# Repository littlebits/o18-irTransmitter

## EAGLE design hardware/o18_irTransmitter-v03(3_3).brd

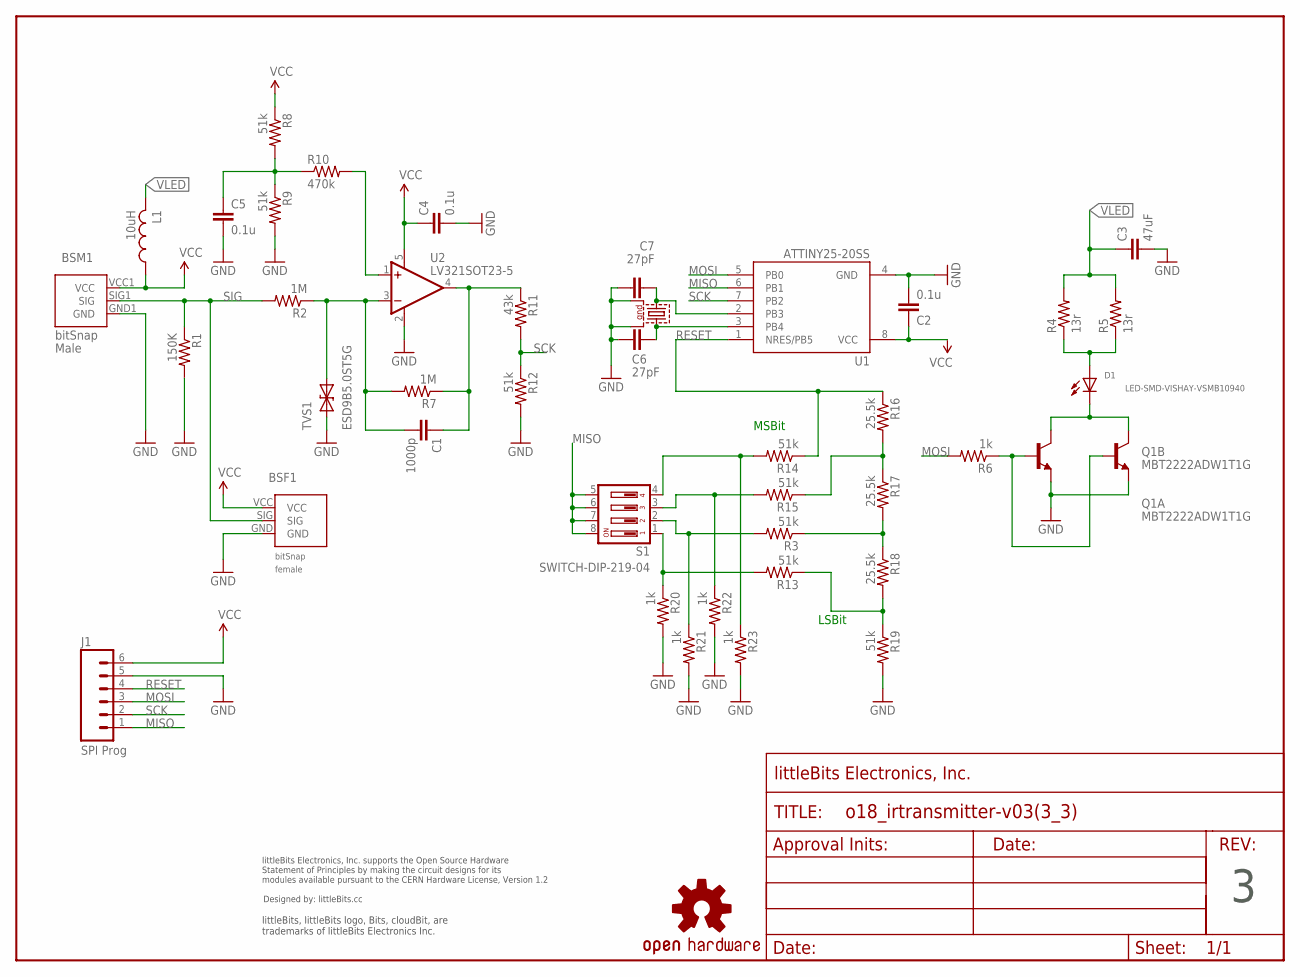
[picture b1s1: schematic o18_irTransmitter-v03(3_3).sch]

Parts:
BSF1: BITSNAP_V03_FEMALE
BSM1: BITSNAP_V03_MALE
C1: 1000p; CAP-0402
C2, C4, C5: 0.1u; CAP-0402
C3: 47uF; CAP-1206
C6, C7: 27pF; CAP-0402
D1: LED-SMD-VISHAY-VSMB10940
J1: SPI Prog; SIP6-SM-0.1IN-NOS.S-MIN
L1: 10uH; IND-0805
Q1: MBT2222ADW1T1G; SOT-363_ONSEMI
R1: 150K; RES-0402
R2, R7: 1M; RES-0402
R3, R8, R9, R12, R13, R14, R15, R19: 51k; RES-0402
R4, R5: 13r; RES-0603
R6, R20, R21, R22, R23: 1k; RES-0402
R10: 470k; RES-0402
R11: 43k; RES-0402
R16, R17, R18: 25.5k; RES-0402
S1: SWITCH-DIP-219-04; CTS-219-04
TVS1: ESD9B5.0ST5G; SOD-923
U1: ATTINY25-20SS; SOIC08_JEDEC_150MIL
U2: LV321SOT23-5; SOT23-5
U$16: OSHWCREDIT
U$26: FRAME-LETTER-OHWOHW; FABDWG01-OHW
U$27: OSHW-LOGOL; OSHW-LOGO-L
X1: 7B-8.000MAAJ-T; CRYSTAL-SMD-7B-SERIES-5X3.2MM

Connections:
GND: BSF1.GND, BSM1.GND1 (GND), C2.2, C3.2, C4.2, C5.2, C6.2, C7.1, J1.5, Q1.1 (E), Q1.4 (E), R1.2, R9.2, R12.2, R19.2, R20.2, R21.2, R22.2, R23.2, TVS1.1 (A), U1.4 (GND), U2.2 (V-), X1.P$2 (2), X1.P$4 (4)
MISO: J1.1, S1.5, S1.6, S1.7, S1.8, U1.6 (PB1)
MOSI: J1.3, R6.2, U1.5 (PB0)
unnamed: D1.C, Q1.3 (C), Q1.6 (C)
unnamed: Q1.2 (B), Q1.5 (B), R6.1
unnamed: D1.A, R4.1, R5.1
unnamed: C1.2, R2.1, R7.2, TVS1.2 (C), U2.3 (-IN)
unnamed: R10.2, U2.1 (+IN)
unnamed: C5.1, R8.2, R9.1, R10.1
unnamed: C1.1, R7.1, R11.1, U2.4 (OUT)
unnamed: C7.2, U1.2 (PB3), X1.P$1 (1)
unnamed: C6.1, U1.3 (PB4), X1.P$3 (3)
unnamed: R3.2, R21.1, S1.2
unnamed: R14.2, R23.1, S1.4
unnamed: R15.2, R22.1, S1.3
unnamed: R13.2, R20.1, S1.1
unnamed: R3.1, R17.2, R18.1
unnamed: R13.1, R18.2, R19.1
unnamed: R15.1, R16.2, R17.1
RESET: J1.4, R14.1, R16.1, U1.1 (NRES/PB5)
SCK: J1.2, R11.2, R12.1, U1.7 (PB2)
SIG: BSF1.SIG, BSM1.SIG1 (SIG), R1.1, R2.2
VCC: BSF1.VCC, BSM1.VCC1 (VCC), C2.1, C4.1, J1.6, L1.1, R8.1, U1.8 (VCC), U2.5 (V+)
VLED: C3.1, L1.2, R4.2, R5.2

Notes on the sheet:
MSBit
LSBit

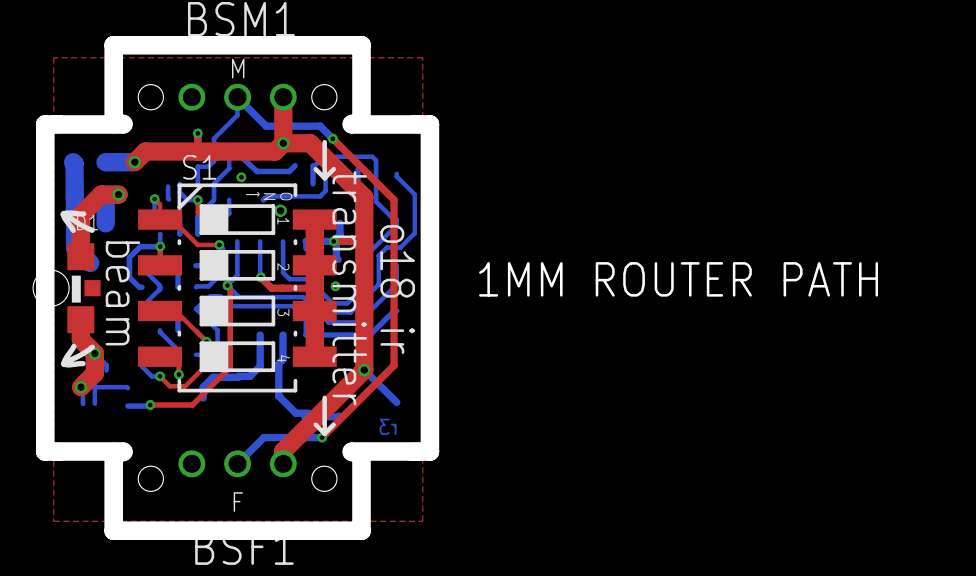
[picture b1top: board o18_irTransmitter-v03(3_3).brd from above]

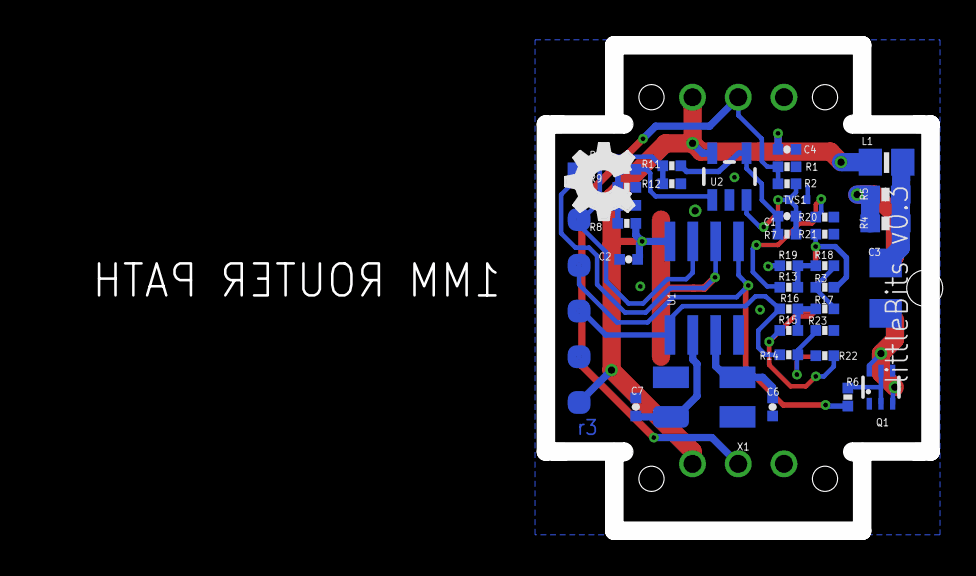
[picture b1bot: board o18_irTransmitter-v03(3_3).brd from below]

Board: 2 copper layers, 49.2 x 27.0 mm, 50 parts (38 on the bottom side), 24 nets.

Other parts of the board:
DRILEGEND: DRILEGEND
U$4, U$21: <
U$5, U$22: L
U$20: OSHW_FILLX150_NOTEXT

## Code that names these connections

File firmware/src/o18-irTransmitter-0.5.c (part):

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	CLKPR = 0x80;		// This two byte combination undoes the CLKDIV setting and sets the clock prescaler to 1,
	CLKPR = 0x00;		// giving us a clock frequency of 8Mhz

	DDRB = ~(_BV(PB2) | _BV(PB5));	// PB2 and PB5 are inputs.
	PORTB = 0;					    // All pins low (keep drive / impedance low and similar from unit to unit)
	
	//Init Timer0 to generate 38 kHz
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		TCCR0A &= ~_BV(COM0A0);			//Disconnect output compare pin
		TIMSK &= ~_BV(OCIE1A);			//Disable output interrupt
		cli();							//disable all interrupts, must turn off output timer interrupt first or the output freaks out
		PORTB &= ~_BV(PB0);				//turn IR off
		wtdgDelay(TX_REP_DEL);
		chanMask = 0;
#endif
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		TCCR0A &= ~_BV(COM0A0);			//Disconnect output compare pin
		TIMSK &= ~_BV(OCIE1A);			//Disable output interrupt
		cli();							//disable all interrupts, must turn off output timer interrupt first or the output freaks out
		PORTB &= ~_BV(PB0);				//turn IR off
		wtdgDelay(TX_REP_DEL);
		chanMask = 0;							
#endif	
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	ADMUX = _BV(MUX3) | _BV(MUX2) | _BV(MUX0);				//Left adjust and set to measure ground (discharge internal cap)
	ADCSRA |= _BV(ADEN) | _BV(ADSC);						//start conversion
	while (ADCSRA & _BV(ADSC)) { asm volatile ("nop"); }	//wait for conversion to finish
	ADMUX = _BV(ADLAR) | _BV(MUX0);							//Left adjusted, Single sided measurement on PB2 referenced to VCC
	DIDR0 |= _BV(ADC1D);									//disConnect digital IO to PB2
	ADCSRA |= _BV(ADEN) | _BV(ADSC);						//start conversion
	while (ADCSRA & _BV(ADSC)) { asm volatile ("nop"); }	//wait for conversion to finish
	DIDR0 &= ~_BV(ADC1D);									//reconnect digital driver
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uint8_t readDIP() {
	uint8_t retVal = 0;
	PRR &= ~_BV(PRADC);										//Power to ADC
	DIDR0 |= _BV(ADC0D);									//disconnect digital IO to PB5
	PORTB |= _BV(PB1);										//Drive DIP switch high
	_delay_us(5);											//wait for DIP voltage to rise
	ADCSRA |= _BV(ADPS2) | _BV(ADPS1);						//configure ADC clock prescaler to divide by 64
	ADMUX = _BV(MUX3) | _BV(MUX2) | _BV(MUX0);				//Left adjust and set to measure ground (discharge internal cap)
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	ADCSRA |= _BV(ADEN) | _BV(ADSC);						//start conversion
	while (ADCSRA & _BV(ADSC)) { asm volatile ("nop"); }	//wait for conversion to finish
	retVal = ADCH;
	ADMUX = _BV(ADLAR);										//Left adjust and set to read PB5, reset must be disabled
	ADCSRA |= _BV(ADEN) | _BV(ADSC);						//start conversion
	while (ADCSRA & _BV(ADSC)) { asm volatile ("nop"); }	//wait for conversion to finish
	retVal = ADCH;
	PORTB &= ~_BV(PB1);										//Turn off DIP switch
	return retVal;
}

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		TCCR0A &= ~_BV(COM0A0);			//Disconnect output compare pin
		TIMSK &= ~_BV(OCIE1A);			//Disable output interrupt
		cli();							//disable all interrupts, must turn off output timer interrupt first or the output freaks out
		PORTB &= ~_BV(PB0);				//turn IR off
		_delay_ms(20);
		if (++numChanReps >= NUM_CHAN_REPS) {
			++chanTrans;					//next channel
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
/* Signal generator */
ISR(TIMER1_COMPA_vect) {
	PORTB &= ~_BV(PB0);				//turn IR off
	TCNT1 = 0;					//Zero both timers to keep waves square
	_NOP();_NOP();_NOP();_NOP();_NOP();_NOP();
	TCNT1 = 0;
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#endif
}

/* Wakeup source PB2 */
EMPTY_INTERRUPT(INT0_vect);
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
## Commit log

2014-11-18 First commit, added hardware and firmware

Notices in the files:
firmware/src/o18-irTransmitter-0.5.c:
Copyright 2014 littleBits Electronics
o18-irTransmitter is free software: you can redistribute it and/or modify
it under the terms of the GNU General Public License as published by
the Free Software Foundation, either version 3 of the License, or
(at your option) any later version.
parts and their libraries:
LITTLEBITS: modules available pursuant to the CERN Hardware License,
Version 1.2
SparkFun: Licensing: CC v3.0 Share-Alike You are welcome to use this library for commercial purposes.
